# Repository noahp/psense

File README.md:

# psense

USB interfaced, 2-channel current + voltage meter.

## Schematic

[Schematic PDF here](psense.pdf)

## Parts

### USB

* USB to I2C interface
* bus powered, no external crystal needed

https://www.ftdichip.com/Products/ICs/FT200XD.html

### Meter

* 2 channel current + bus voltage (0-40V)
* I2C interface
* adjustable range +/-10mV, 20mV, 40mV, 80mV

http://www.mouser.com/ProductDetail/Microchip/PAC1720-1-AIA-TR

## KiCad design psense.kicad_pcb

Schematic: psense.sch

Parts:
C1: 0.1µF; C_0603_1608Metric
C2: 10pF; C_0603_1608Metric
C3: 100nF; C_0603_1608Metric
J1: USB_B_Micro; USB_Micro-B_Molex_47346-0001
R1, R3: 0.1R; R_0603_1608Metric
R2, R4: 1.0R; R_0603_1608Metric
R5, R6: 1K; R_0603_1608Metric
TP1: S1_OUT; PinHeader_1x01_P2.54mm_Horizontal
TP2: S1_SEL_H; PinHeader_1x01_P2.54mm_Horizontal
TP3: S1_SEL_L; PinHeader_1x01_P2.54mm_Horizontal
TP4: S1_SEL_C; PinHeader_1x01_P2.54mm_Horizontal
TP5: S1_IN; PinHeader_1x01_P2.54mm_Horizontal
TP6: S2_OUT; PinHeader_1x01_P2.54mm_Horizontal
TP7: S2_SEL_H; PinHeader_1x01_P2.54mm_Horizontal
TP8: S2_SEL_L; PinHeader_1x01_P2.54mm_Horizontal
TP9: S2_SEL_C; PinHeader_1x01_P2.54mm_Horizontal
TP10: S2_IN; PinHeader_1x01_P2.54mm_Horizontal
U1: PAC1720; DFN-10-1EP_2x3mm_P0.5mm_EP0.64x2.4mm
U2: FT200XD; DFN-10-1EP_3x3mm_P0.5mm_EP1.55x2.48mm

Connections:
/ADDR_SEL: U1.6 (ADDR_SEL)
/FT200XD_VCCIO: C3.1, R5.1, R6.1, U2.2, U2.3, U2.7
/I2C_SCL: R5.2, U1.9 (SMCLK), U2.6
/I2C_SDA: R6.2, U1.8 (SMDATA), U2.8
/SENSE1+: TP4.1, TP5.1, U1.1 (SENSE1+)
/SENSE1-: R1.2, R2.2, TP1.1, U1.2 (SENSE1-)
/SENSE2+: TP9.1, TP10.1, U1.3 (SENSE2+)
/SENSE2-: R3.2, R4.2, TP6.1, U1.4 (SENSE2-)
/USB_DM: J1.2, U2.1
/USB_DP: J1.3, U2.10
/USB_VBUS: C1.1, C2.1, J1.1, U1.10 (VDD), U2.4
/~ALERT: U1.7 (~ALERT)
GND: C1.2, C2.2, C3.2, J1.5, U1.5 (GND), U2.9, U2.11
unnamed: R1.1, TP2.1
unnamed: R2.1, TP3.1
unnamed: R3.1, TP7.1
unnamed: R4.1, TP8.1

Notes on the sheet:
I2C Pullups
Sense Networks
Sampling freq 2.5ms 80ms(default) R= 0.1 ohm ADC bits= 6 11 mV range A range Resolution 10 +/- 0.1 A 1.587301587 0.04885197851 mA 20 +/- 0.2 A 3.174603175 0.09770395701 mA 40 +/- 0.4 A 6.349206349 0.195407914 mA 80 +/- 0.8 A 12.6984127 0.390815828 mA
Sampling freq 2.5ms 80ms(default) R= 1 ohm ADC bits= 6 11 mV range A range Resolution 10 +/- 0.01 A 0.1587301587 0.004885197851 mA 20 +/- 0.02 A 0.3174603175 0.009770395701 mA 40 +/- 0.04 A 0.6349206349 0.0195407914 mA 80 +/- 0.08 A 1.26984127 0.0390815828 mA
*nb place close to Vdd pins on ICs

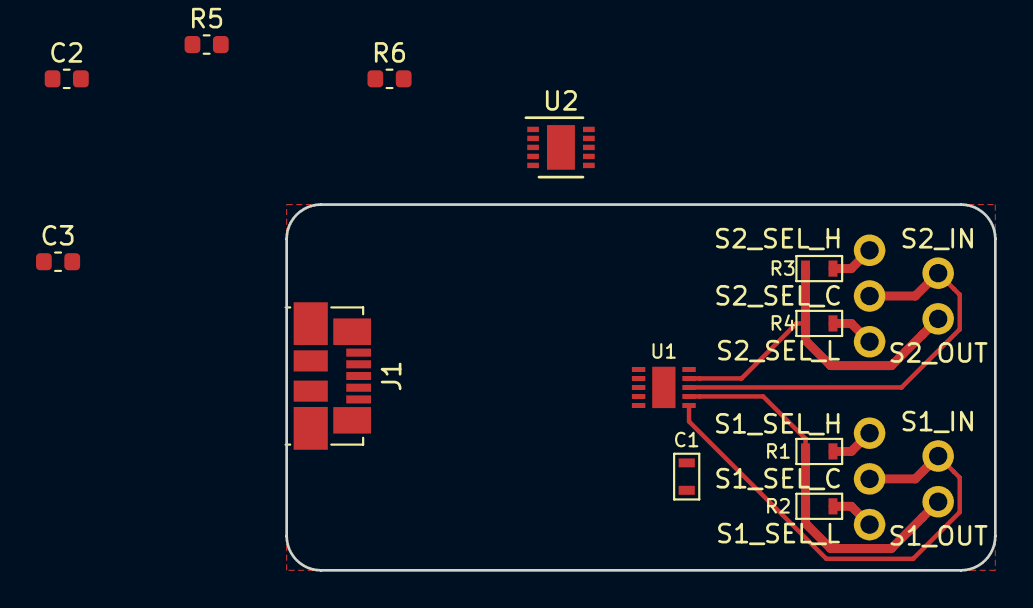
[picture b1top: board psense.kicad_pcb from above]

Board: 2 copper layers, 39.4 x 20.3 mm, 22 parts (0 on the bottom side), 15 nets.

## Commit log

2017-02-08 Add candidate parts
2017-02-09 Add kicadlib submodule
2017-02-09 Add power sense IC and MCU
2017-02-12 Swap mcu for plain old usb-i2c converter
2017-02-12 Update MCP2221 component
2017-02-12 Most of schematic done
2017-02-12 Finish schematic
2017-02-12 Add gitignore
2017-02-12 No more sw! rearrange
2017-02-12 Link to schematic
2017-02-12 Layout done
2017-02-12 Add psense.kicad_pcb-bak to gitignore
2017-02-13 Rename
2017-02-13 Tidy up a bit
2017-02-14 Add title page to schematic
2017-02-18 Add partially working sample USB interface code
2017-02-19 Add some windows support, not working yet
2017-03-11 Fix https://github.com/noahp/psense/issues/1 https://github.com/noahp/psense/issues/2 https://github.com/noahp/psense/issues/3
2017-03-11 Update render
2017-04-02 Windows USB interface now works, need to test on linux + mac next
2017-10-15 Format per pep8
2019-04-06 Use FT200XD instead
